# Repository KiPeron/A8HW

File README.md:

A8HW

Just wrist watch on atmega 8

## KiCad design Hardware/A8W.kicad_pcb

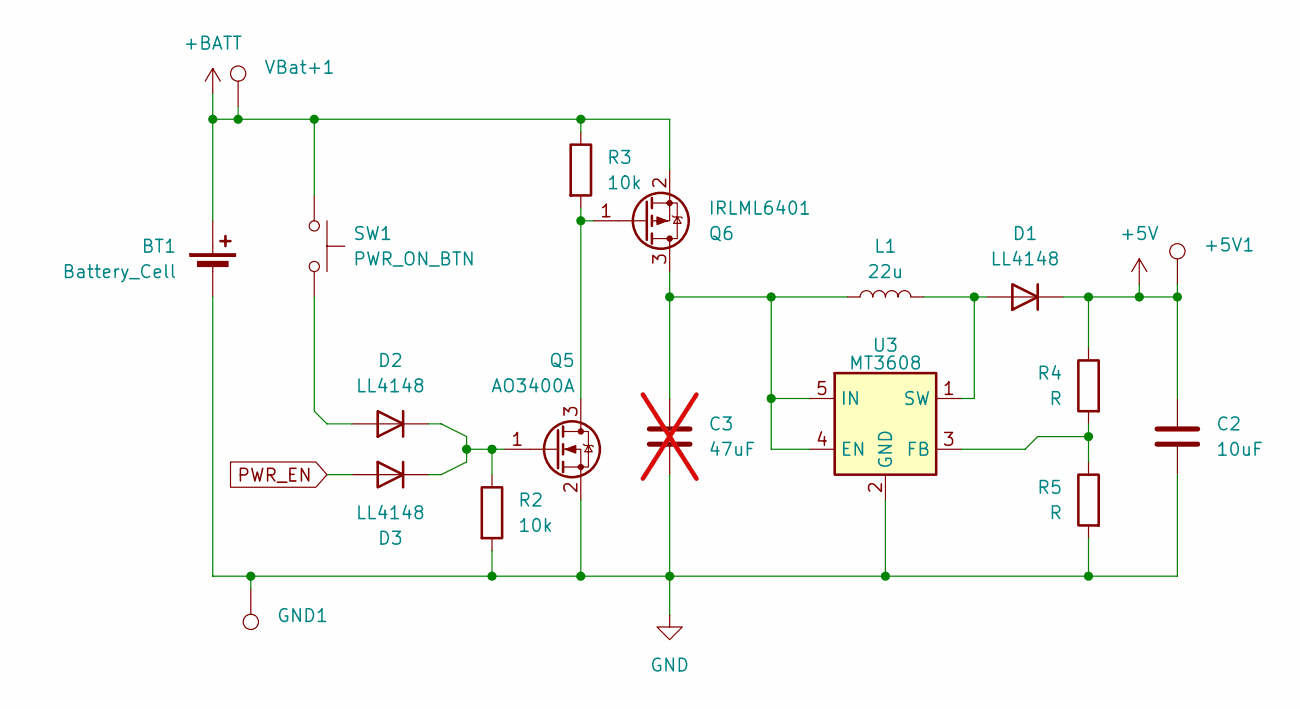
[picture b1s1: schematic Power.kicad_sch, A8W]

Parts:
+5V1: TestPoint_Pad_D2.0mm
BT1: Battery_Cell; BatteryHolder_Keystone_3034_1x20mm
C2: 10uF; C_1206_3216Metric
C3: 47uF; CP_EIA-7343-30_AVX-N_Pad2.25x2.55mm_HandSolder; not fitted
D1, D2, D3: LL4148; D_MiniMELF
GND1: TestPoint_Pad_D2.0mm
L1: 22u; L_Cenker_CKCS3015
Q5: AO3400A; SOT-23
Q6: IRLML6401; SOT-23
R2, R3: 10k; R_1206_3216Metric
R4, R5: R; R_1206_3216Metric
SW1: PWR_ON_BTN; SW_Push_1P1T_XKB_TS-1187A
U3: MT3608; SOT-23-6
VBat+1: TestPoint_Pad_D2.0mm

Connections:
+5V: +5V1.1, C2.1, D1.1 (K), R4.1; also elsewhere on the board
GND: BT1.2 (-), C2.2, C3.2, GND1.1, Q5.2 (S), R2.2, R5.2, U3.2 (GND); also elsewhere on the board
unnamed: D1.2 (A), L1.2, U3.1 (SW)
unnamed: D2.2 (A), SW1.2
unnamed: D2.1 (K), D3.1 (K), Q5.1 (G), R2.1
unnamed: Q5.3 (D), Q6.1 (G), R3.2
unnamed: R4.2, R5.1, U3.3 (FB)
PWR_EN: D3.2 (A); also elsewhere on the board

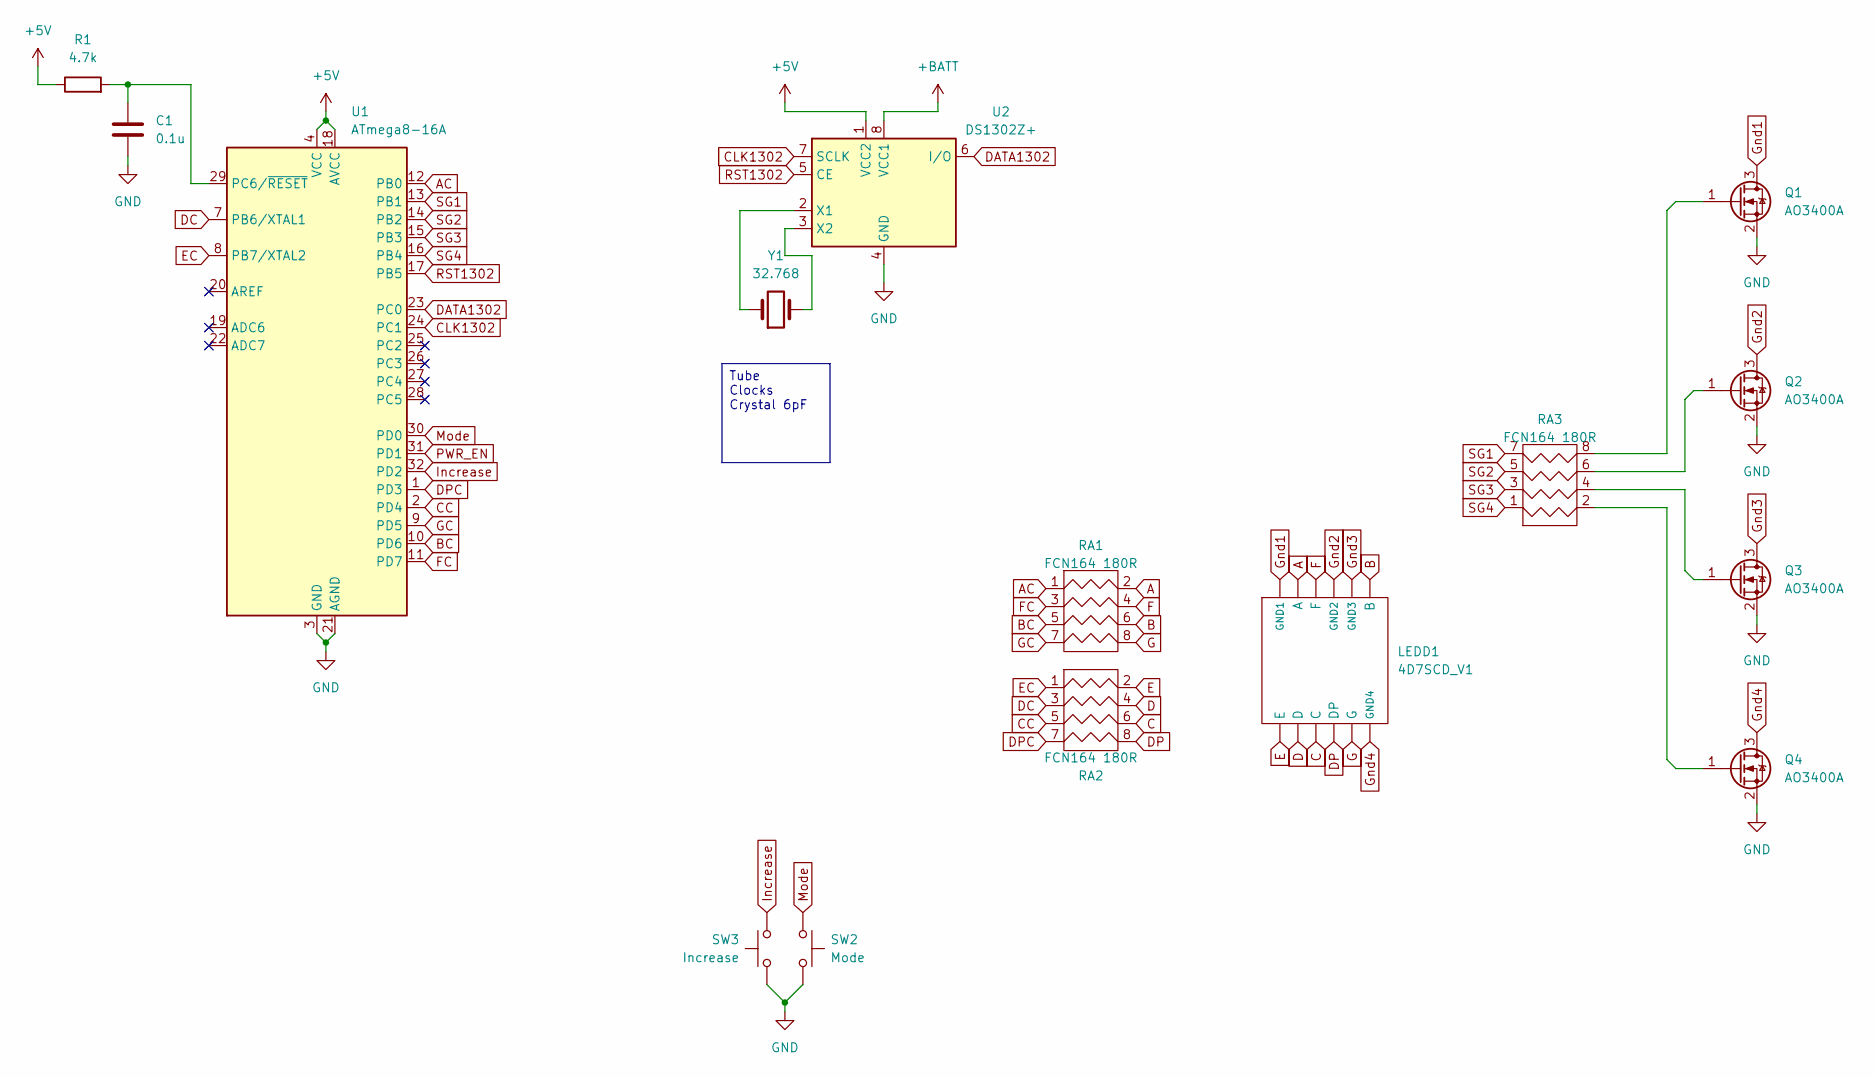
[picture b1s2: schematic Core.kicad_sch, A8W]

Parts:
C1: 0.1u; C_0603_1608Metric
LEDD1: 4D7SCD_V1; 4D7SCD_V1_SMD
Q1, Q2, Q3, Q4: AO3400A; SOT-23
R1: 4.7k; R_1206_3216Metric
RA1, RA2, RA3: FCN164 180R; FCN164
SW2: Mode; SW_Push_1P1T_XKB_TS-1187A
SW3: Increase; SW_Push_1P1T_XKB_TS-1187A
U1: ATmega8-16A; TQFP-32_7x7mm_P0.8mm
U2: DS1302Z+; SOIC-8_3.9x4.9mm_P1.27mm
Y1: 32.768; Crystal_C38-LF_D3.0mm_L8.0mm_Horizontal

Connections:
+5V: R1.1, U1.4 (VCC), U1.6 (VCC), U1.18 (AVCC), U2.1 (VCC2); also elsewhere on the board
A: LEDD1.2 (A), RA1.2
AC: RA1.1, U1.12 (PB0)
B: LEDD1.6 (B), RA1.6
BC: RA1.5, U1.10 (PD6)
C: LEDD1.10 (C), RA2.6
CC: RA2.5, U1.2 (PD4)
CLK1302: U1.24 (PC1), U2.7 (SCLK)
D: LEDD1.11 (D), RA2.4
DATA1302: U1.23 (PC0), U2.6 (I/O)
DC: RA2.3, U1.7 (PB6/XTAL1)
DP: LEDD1.9 (DP), RA2.8
DPC: RA2.7, U1.1 (PD3)
E: LEDD1.12 (E), RA2.2
EC: RA2.1, U1.8 (PB7/XTAL2)
F: LEDD1.3 (F), RA1.4
FC: RA1.3, U1.11 (PD7)
G: LEDD1.8 (G), RA1.8
GC: RA1.7, U1.9 (PD5)
GND: C1.2, Q1.2 (S), Q2.2 (S), Q3.2 (S), Q4.2 (S), SW2.2, SW3.2, U1.3 (GND), U1.5 (GND), U1.21 (AGND), U2.4 (GND); also elsewhere on the board
Gnd1: LEDD1.1 (GND1), Q1.3 (D)
Gnd2: LEDD1.4 (GND2), Q2.3 (D)
Gnd3: LEDD1.5 (GND3), Q3.3 (D)
Gnd4: LEDD1.7 (GND4), Q4.3 (D)
Increase: SW3.1, U1.32 (PD2)
Mode: SW2.1, U1.30 (PD0)
unnamed: Q1.1 (G), RA3.8
unnamed: Q2.1 (G), RA3.6
unnamed: Q3.1 (G), RA3.4
unnamed: Q4.1 (G), RA3.2
unnamed: C1.1, R1.2, U1.29 (PC6/~RESET)
unnamed: U2.2 (X1), Y1.1
unnamed: U2.3 (X2), Y1.2
PWR_EN: U1.31 (PD1); also elsewhere on the board
RST1302: U1.17 (PB5), U2.5 (CE)
SG1: RA3.7, U1.13 (PB1)
SG2: RA3.5, U1.14 (PB2)
SG3: RA3.3, U1.15 (PB3)
SG4: RA3.1, U1.16 (PB4)

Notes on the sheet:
Tube Clocks Crystal 6pF

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
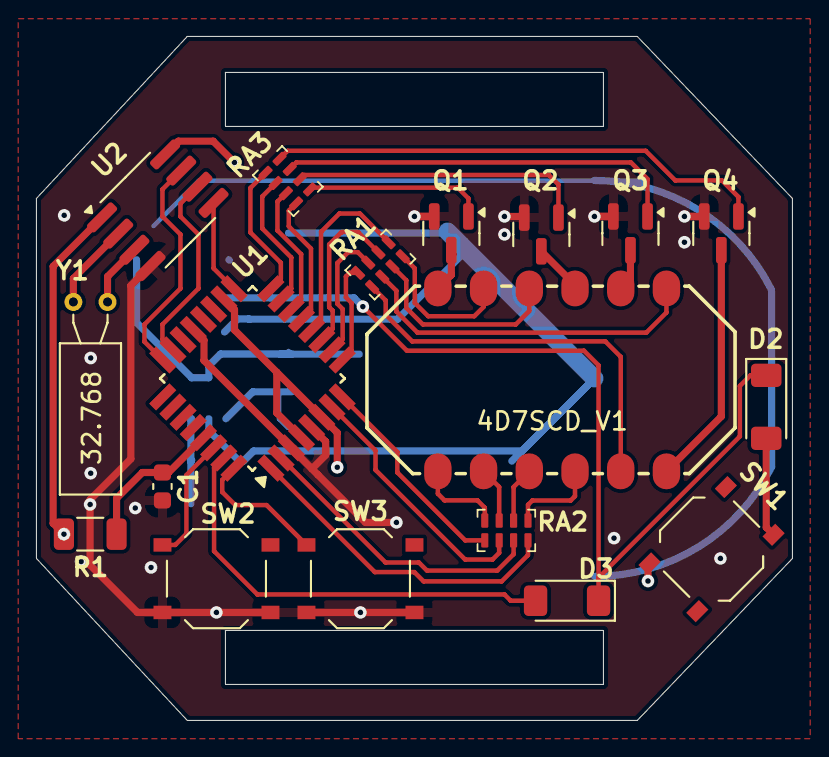
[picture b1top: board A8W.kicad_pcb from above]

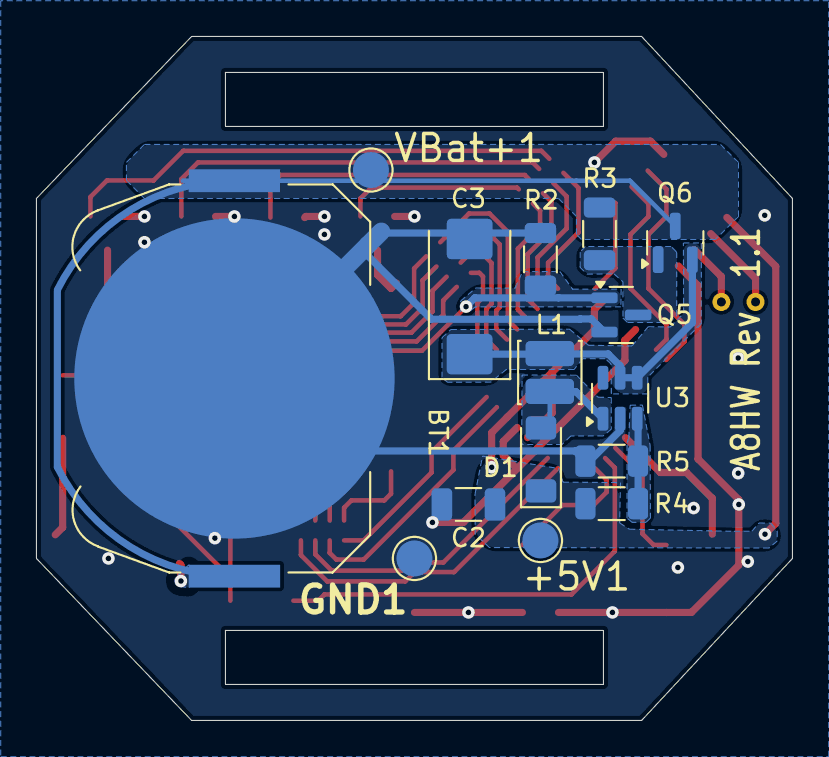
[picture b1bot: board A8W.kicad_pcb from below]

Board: 2 copper layers, 42.0 x 38.0 mm, 33 parts (15 on the bottom side), 46 nets.
